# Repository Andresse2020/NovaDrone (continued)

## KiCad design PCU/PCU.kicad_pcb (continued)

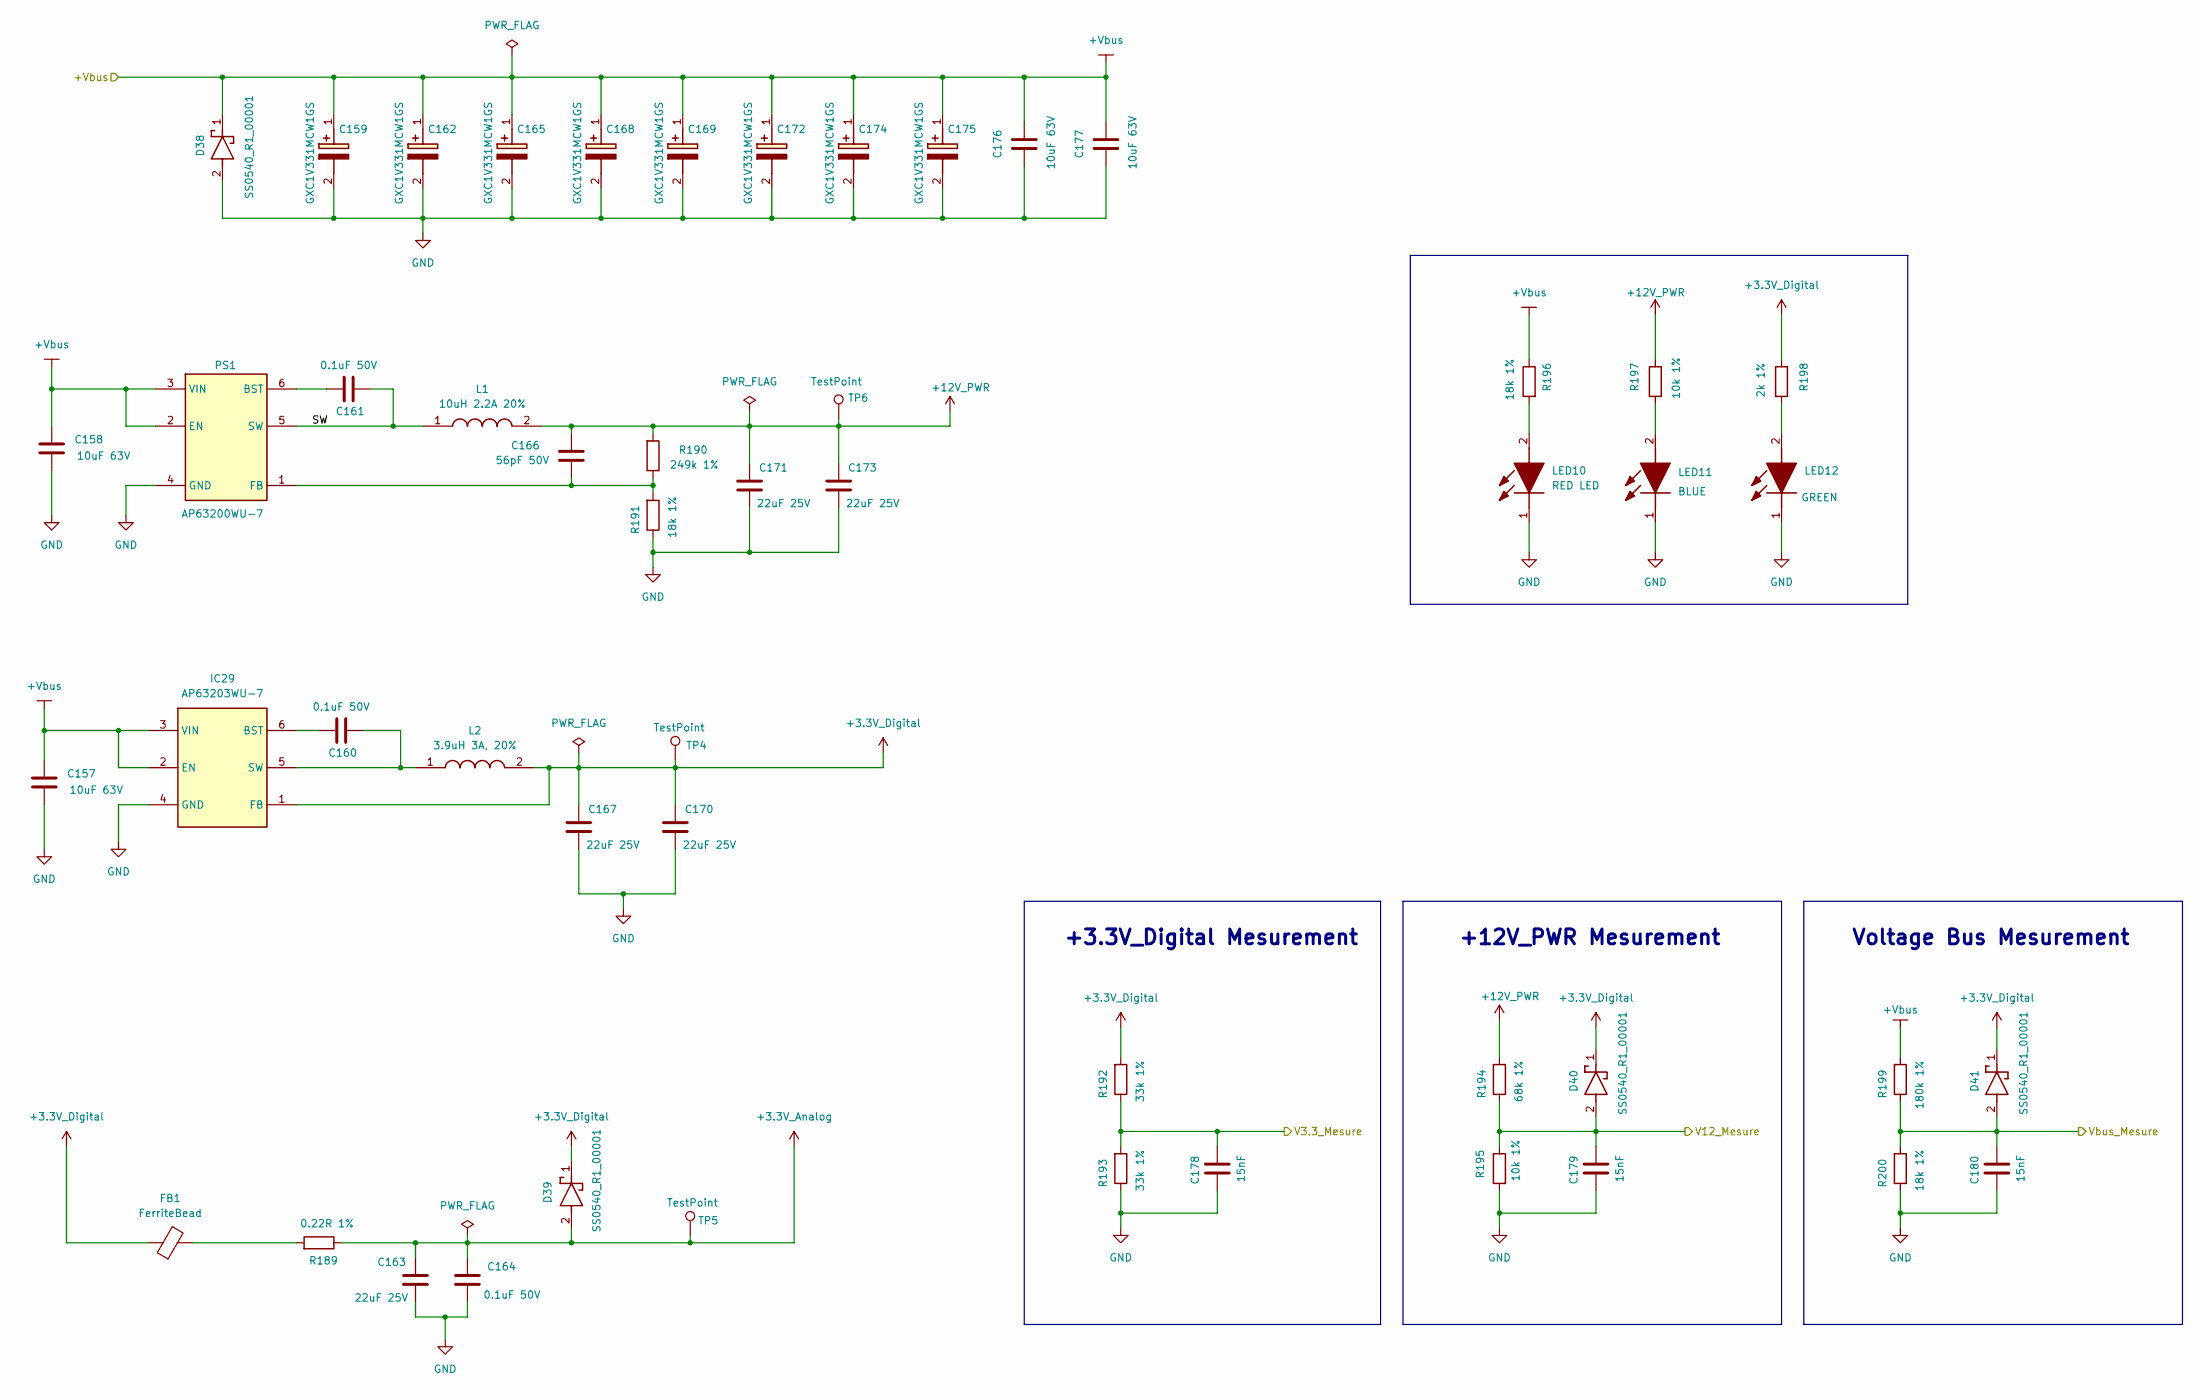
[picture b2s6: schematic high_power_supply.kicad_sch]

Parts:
C157, C158, C176, C177: 10uF 63V; C_1210_3225Metric; Manufacturer_Part_Number CL32B106KMVNNWE
C159, C162, C165, C168, C169, C172, C174, C175: GXC1V331MCW1GS; CAPAE1030X1300N; Mouser Part Number 647-GXC1V331MCW1GS
C160, C161, C164: 0.1uF 50V; C_0603_1608Metric; Manufacturer_Part_Number CL10B104KB85PNL
C163, C167, C170, C171, C173: 22uF 25V; C_1210_3225Metric; Manufacturer_Part_Number CL32B226KAJNNNE
C166: 56pF 50V; C_0603_1608Metric; Manufacturer_Part_Number CL10C560JB8NNNC
C178, C179, C180: 15nF; C_0603_1608Metric; Manufacturer_Part_Number CL10B153KB8NNNC
D38, D39, D40, D41: SS0540_R1_00001; SOD3816X135N; Mouser Part Number 241-SS0540_R1_00001
FB1: FerriteBead; L_0805_2012Metric; Manufacturer_Part_Number MPZ2012S601AT000
IC29: AP63203WU-7; AP63203WU7; Mouser Part Number 621-AP63203WU-7
L1: 10uH 2.2A 20%; BWVS00505040100M00; Manufacturer_Part_Number BWVS00505040100M00
L2: 3.9uH 3A, 20%; ASPI0628150MT1; Mouser Part Number 815-ASPI-0628-3R9MT1
LED10: RED LED; LEDM168X80N; Manufacturer_Part_Number APHD1608LSURCK
LED11: BLUE; LEDM168X80N; Mouser Part Number 604-APHD1608LQBCD
LED12: GREEN; LEDM168X80N; Mouser Part Number 604-APHD1608LZGCK
PS1: AP63200WU-7; SOT95P280X100-6N; Mouser Part Number 621-AP63200WU-7
R189: 0.22R 1%; R_0805_2012Metric; Manufacturer_Part_Number RL0805FR-7W0R22L
R190: 249k 1%; R_0603_1608Metric; Manufacturer_Part_Number AF0603FR-07249KL
R191, R196, R200: 18k 1%; R_0603_1608Metric; Manufacturer_Part_Number AC0603FR-1318KL
R192, R193: 33k 1%; R_0603_1608Metric; Manufacturer_Part_Number AC0603FR-1333KL
R194: 68k 1%; R_0603_1608Metric; Manufacturer_Part_Number RC0603FR-1068KL
R195, R197: 10k 1%; R_0603_1608Metric; Manufacturer_Part_Number AF0603FR-0710KL
R198: 2k 1%; R_0603_1608Metric; Manufacturer_Part_Number RE0603FRE072KL
R199: 180k 1%; R_0603_1608Metric; Manufacturer_Part_Number RT0603FRE07180KL
TP4, TP5, TP6: TestPoint; TestPoint_Pad_D1.0mm

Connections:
+3.3V_Analog: C163.2, C164.2, D39.2 (A), R189.1, TP5.1; also elsewhere on the board
+3.3V_Digital: C167.2, C170.2, D39.1 (K), D40.1 (K), D41.1 (K), FB1.1, IC29.1 (FB), L2.2, R192.2, R198.1, TP4.1; also elsewhere on the board
+12V_PWR: C166.2, C171.2, C173.2, L1.2, R190.2, R194.2, R197.1, TP6.1; also elsewhere on the board
+Vbus: C157.2, C158.2, C159.1 (+), C162.1 (+), C165.1 (+), C168.1 (+), C169.1 (+), C172.1 (+), C174.1 (+), C175.1 (+), C176.2, C177.2, D38.1 (K), IC29.2 (EN), IC29.3 (VIN), PS1.2 (EN), PS1.3 (VIN), R196.1, R199.2; also elsewhere on the board
/HIGH PSU/SW: C161.1, L1.1, PS1.5 (SW)
/HIGH PSU/V3.3_Mesure: C178.2, R192.1, R193.2; also elsewhere on the board
/HIGH PSU/V12_Mesure: C179.2, D40.2 (A), R194.1, R195.1; also elsewhere on the board
/HIGH PSU/Vbus_Mesure: C180.2, D41.2 (A), R199.1, R200.2; also elsewhere on the board
GND: C157.1, C158.1, C159.2 (-), C162.2 (-), C163.1, C164.1, C165.2 (-), C167.1, C168.2 (-), C169.2 (-), C170.1, C171.1, C172.2 (-), C173.1, C174.2 (-), C175.2 (-), C176.1, C177.1, C178.1, C179.1, C180.1, D38.2 (A), IC29.4 (GND), LED10.1 (K), LED11.1 (K), LED12.1 (K), PS1.4 (GND), R191.1, R193.1, R195.2, R200.1; also elsewhere on the board
unnamed: FB1.2, R189.2
unnamed: C160.2, IC29.6 (BST)
unnamed: C160.1, IC29.5 (SW), L2.1
unnamed: LED10.2 (A), R196.2
unnamed: LED11.2 (A), R197.2
unnamed: LED12.2 (A), R198.2
unnamed: C161.2, PS1.6 (BST)
unnamed: C166.1, PS1.1 (FB), R190.1, R191.2

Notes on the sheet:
+3.3V_Digital Mesurement
Voltage Bus Mesurement
+12V_PWR Mesurement

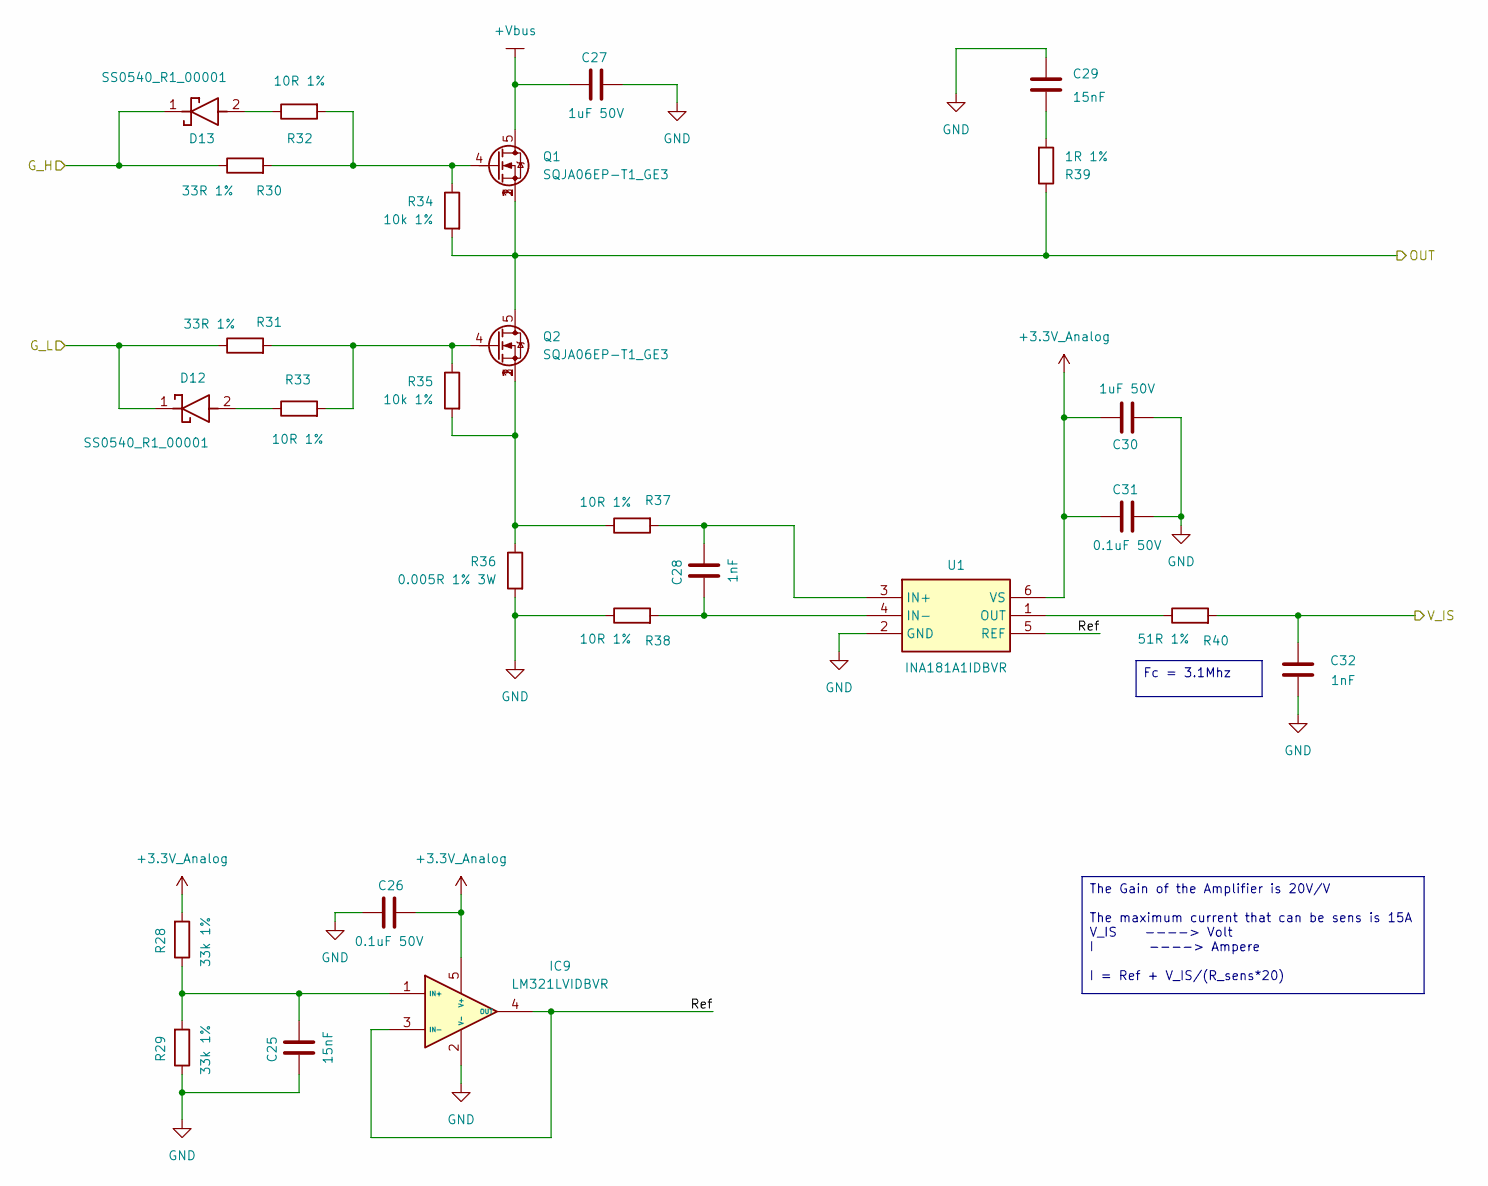
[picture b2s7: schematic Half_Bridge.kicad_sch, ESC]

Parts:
C25, C29: 15nF; C_0603_1608Metric; Manufacturer_Part_Number CL10B153KB8NNNC
C26, C31: 0.1uF 50V; C_0603_1608Metric; Manufacturer_Part_Number CL10B104KB85PNL
C27, C30: 1uF 50V; C_0805_2012Metric; Manufacturer_Part_Number CL21B105KBFNNNE
C28, C32: 1nF; C_0603_1608Metric; Manufacturer_Part_Number KAF15AR71H102KM
D12, D13: SS0540_R1_00001; SOD3816X135N; Mouser Part Number 241-SS0540_R1_00001
IC9: LM321LVIDBVR; SOT95P280X145-5N; Mouser Part Number 595-LM321LVIDBVR
Q1, Q2: SQJA06EP-T1_GE3; SQJ402EPT1; Manufacturer_Part_Number SQJA06EP-T1_GE3
R28, R29: 33k 1%; R_0603_1608Metric; Manufacturer_Part_Number AC0603FR-1333KL
R30, R31: 33R 1%; R_0603_1608Metric; Manufacturer_Part_Number AF0603FR-0733RL
R32, R33, R37, R38: 10R 1%; R_0603_1608Metric; Manufacturer_Part_Number RE0603FRE0710RL
R34, R35: 10k 1%; R_0603_1608Metric; Manufacturer_Part_Number AF0603FR-0710KL
R36: 0.005R 1% 3W; R_2512_6332Metric; Manufacturer_Part_Number MSMA2512R0050FGM
R39: 1R 1%; R_0603_1608Metric; Manufacturer_Part_Number AF0603FR-071RL
R40: 51R 1%; R_0603_1608Metric; Manufacturer_Part_Number RT0603FRE0751RL
U1: INA181A1IDBVR; SOT95P280X145-6N; Mouser Part Number 595-INA181A1IDBVR

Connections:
+3.3V_Analog: C26.1, C30.1, C31.1, IC9.5 (V+), R28.2, U1.6 (VS); also elsewhere on the board
+Vbus: C27.1, Q1.5; also elsewhere on the board
/ESC_2/Current_Sens_2: C32.2, R40.2; also elsewhere on the board
/ESC_2/Half-Bridge_2/G_H: D13.1 (K), R30.1; also elsewhere on the board
/ESC_2/Half-Bridge_2/G_L: D12.1 (K), R31.1; also elsewhere on the board
/ESC_2/Half-Bridge_2/Ref: IC9.3 (IN-), IC9.4 (OUT), U1.5 (REF)
/ESC_2/OUT2: Q1.1, Q1.2, Q1.3, Q2.5, R34.2, R39.1; also elsewhere on the board
GND: C25.1, C26.2, C27.2, C29.1, C30.2, C31.2, C32.1, IC9.2 (V-), R29.1, R36.2, R38.1, U1.2 (GND); also elsewhere on the board
unnamed: C29.2, R39.2
unnamed: D12.2 (A), R33.1
unnamed: D13.2 (A), R32.1
unnamed: C25.2, IC9.1 (IN+), R28.1, R29.2
unnamed: Q1.4, R30.2, R32.2, R34.1
unnamed: Q2.1, Q2.2, Q2.3, R35.2, R36.1, R37.1
unnamed: Q2.4, R31.2, R33.2, R35.1
unnamed: C28.2, R37.2, U1.3 (IN+)
unnamed: C28.1, R38.2, U1.4 (IN-)
unnamed: R40.1, U1.1 (OUT)

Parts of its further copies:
C33, C37, C41, C45, C73, C77, C81, C85, C89, C93, C121, C125, C129, C133, C137, C141, C194, C200, C206, C220, C235, C248: 15nF; C_0603_1608Metric; Manufacturer_Part_Number CL10B153KB8NNNC
C34, C39, C42, C47, C74, C79, C82, C87, C90, C95, C122, C127, C130, C135, C138, C143, C195, C202, C210, C224, C237, C251: 0.1uF 50V; C_0603_1608Metric; Manufacturer_Part_Number CL10B104KB85PNL
C35, C38, C43, C46, C75, C78, C83, C86, C91, C94, C123, C126, C131, C134, C139, C142, C197, C201, C211, C223, C240, C250: 1uF 50V; C_0805_2012Metric; Manufacturer_Part_Number CL21B105KBFNNNE
C36, C40, C44, C48, C76, C80, C84, C88, C92, C96, C124, C128, C132, C136, C140, C144, C198, C204, C216, C228, C242, C253: 1nF; C_0603_1608Metric; Manufacturer_Part_Number KAF15AR71H102KM
D14, D15, D16, D17, D22, D23, D24, D25, D26, D27, D32, D33, D34, D35, D36, D37, D42, D43, D45, D46, D49, D50: SS0540_R1_00001; SOD3816X135N; Mouser Part Number 241-SS0540_R1_00001
IC10, IC11, IC17, IC18, IC19, IC25, IC26, IC27, IC31, IC33, IC37: LM321LVIDBVR; SOT95P280X145-5N; Mouser Part Number 595-LM321LVIDBVR
Q3, Q4, Q5, Q6, Q7, Q8, Q9, Q10, Q11, Q12, Q13, Q14, Q15, Q16, Q17, Q18, Q19, Q20, Q28, Q29, Q30, Q31: SQJA06EP-T1_GE3; SQJ402EPT1; Manufacturer_Part_Number SQJA06EP-T1_GE3
R41, R42, R54, R55, R86, R87, R99, R100, R112, R113, R144, R145, R157, R158, R170, R171, R208, R209, R239, R240, R266, R267: 33k 1%; R_0603_1608Metric; Manufacturer_Part_Number AC0603FR-1333KL
R43, R44, R56, R57, R88, R89, R101, R102, R114, R115, R146, R147, R159, R160, R172, R173, R210, R211, R241, R242, R268, R269: 33R 1%; R_0603_1608Metric; Manufacturer_Part_Number AF0603FR-0733RL
R45, R46, R50, R51, R58, R59, R63, R64, R90, R91, R95, R96, R103, R104, R108, R109, R116, R117, R121, R122, R148, R149, R153, R154, R161, R162, R166, R167, R174, R175, R179, R180, R212, R213, R223, R224, R243, R244, R250, R251, R270, R271, R277, R278: 10R 1%; R_0603_1608Metric; Manufacturer_Part_Number RE0603FRE0710RL
R47, R48, R60, R61, R92, R93, R105, R106, R118, R119, R150, R151, R163, R164, R176, R177, R217, R218, R245, R246, R273, R274: 10k 1%; R_0603_1608Metric; Manufacturer_Part_Number AF0603FR-0710KL
R49, R62, R94, R107, R120, R152, R165, R178, R219, R247, R275: 0.005R 1% 3W; R_2512_6332Metric; Manufacturer_Part_Number MSMA2512R0050FGM
R52, R65, R97, R110, R123, R155, R168, R181, R231, R254, R280: 1R 1%; R_0603_1608Metric; Manufacturer_Part_Number AF0603FR-071RL
R53, R66, R98, R111, R124, R156, R169, R182, R234, R257, R281: 51R 1%; R_0603_1608Metric; Manufacturer_Part_Number RT0603FRE0751RL
U2, U3, U4, U5, U6, U7, U8, U9, U10, U11, U12: INA181A1IDBVR; SOT95P280X145-6N; Mouser Part Number 595-INA181A1IDBVR

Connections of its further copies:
+3.3V_Analog: C34.1, C38.1, C39.1, C42.1, C46.1, C47.1, C74.1, C78.1, C79.1, C82.1, C86.1, C87.1, C90.1, C94.1, C95.1, C122.1, C126.1, C127.1, C130.1, C134.1, C135.1, C138.1, C142.1, C143.1, C195.1, C201.1, C202.1, C210.1, C223.1, C224.1, C237.1, C250.1, C251.1, IC10.5 (V+), IC11.5 (V+), IC17.5 (V+), IC18.5 (V+), IC19.5 (V+), IC25.5 (V+), IC26.5 (V+), IC27.5 (V+), IC31.5 (V+), IC33.5 (V+), IC37.5 (V+), R41.2, R54.2, R86.2, R99.2, R112.2, R144.2, R157.2, R170.2, R208.2, R239.2, R266.2, U2.6 (VS), U3.6 (VS), U4.6 (VS), U5.6 (VS), U6.6 (VS), U7.6 (VS), U8.6 (VS), U9.6 (VS), U10.6 (VS), U11.6 (VS), U12.6 (VS); also elsewhere on the board
+Vbus: C35.1, C43.1, C75.1, C83.1, C91.1, C123.1, C131.1, C139.1, C197.1, C211.1, C240.1, Q3.5, Q5.5, Q7.5, Q9.5, Q11.5, Q13.5, Q15.5, Q17.5, Q19.5, Q28.5, Q30.5; also elsewhere on the board
/ESC_1/Current_Sens_1: C204.2, R234.2; also elsewhere on the board
/ESC_1/Current_Sens_2: C228.2, R257.2; also elsewhere on the board
/ESC_1/Current_Sens_3: C253.2, R281.2; also elsewhere on the board
/ESC_1/Half-Bridge_1/G_H: D43.1 (K), R210.1; also elsewhere on the board
/ESC_1/Half-Bridge_1/G_L: D42.1 (K), R211.1; also elsewhere on the board
/ESC_1/Half-Bridge_1/Ref: IC31.3 (IN-), IC31.4 (OUT), U10.5 (REF)
/ESC_1/Half-Bridge_2/G_H: D46.1 (K), R241.1; also elsewhere on the board
/ESC_1/Half-Bridge_2/G_L: D45.1 (K), R242.1; also elsewhere on the board
/ESC_1/Half-Bridge_2/Ref: IC33.3 (IN-), IC33.4 (OUT), U11.5 (REF)
/ESC_1/Half-Bridge_3/G_H: D50.1 (K), R268.1; also elsewhere on the board
/ESC_1/Half-Bridge_3/G_L: D49.1 (K), R269.1; also elsewhere on the board
/ESC_1/Half-Bridge_3/Ref: IC37.3 (IN-), IC37.4 (OUT), U12.5 (REF)
/ESC_1/OUT1: Q19.1, Q19.2, Q19.3, Q20.5, R217.2, R231.1; also elsewhere on the board
/ESC_1/OUT2: Q28.1, Q28.2, Q28.3, Q29.5, R245.2, R254.1; also elsewhere on the board
/ESC_1/OUT3: Q30.1, Q30.2, Q30.3, Q31.5, R273.2, R280.1; also elsewhere on the board
/ESC_2/Current_Sens_1: C40.2, R53.2; also elsewhere on the board
/ESC_2/Current_Sens_3: C48.2, R66.2; also elsewhere on the board
/ESC_2/Half-Bridge_1/G_H: D15.1 (K), R43.1; also elsewhere on the board
/ESC_2/Half-Bridge_1/G_L: D14.1 (K), R44.1; also elsewhere on the board
/ESC_2/Half-Bridge_1/Ref: IC10.3 (IN-), IC10.4 (OUT), U2.5 (REF)
/ESC_2/Half-Bridge_3/G_H: D17.1 (K), R56.1; also elsewhere on the board
/ESC_2/Half-Bridge_3/G_L: D16.1 (K), R57.1; also elsewhere on the board
/ESC_2/Half-Bridge_3/Ref: IC11.3 (IN-), IC11.4 (OUT), U3.5 (REF)
/ESC_2/OUT1: Q3.1, Q3.2, Q3.3, Q4.5, R47.2, R52.1; also elsewhere on the board
/ESC_2/OUT3: Q5.1, Q5.2, Q5.3, Q6.5, R60.2, R65.1; also elsewhere on the board
/ESC_3/Current_Sens_1: C88.2, R111.2; also elsewhere on the board
/ESC_3/Current_Sens_2: C80.2, R98.2; also elsewhere on the board
/ESC_3/Current_Sens_3: C96.2, R124.2; also elsewhere on the board
/ESC_3/Half-Bridge_1/G_H: D25.1 (K), R101.1; also elsewhere on the board
/ESC_3/Half-Bridge_1/G_L: D24.1 (K), R102.1; also elsewhere on the board
/ESC_3/Half-Bridge_1/Ref: IC18.3 (IN-), IC18.4 (OUT), U5.5 (REF)
/ESC_3/Half-Bridge_2/G_H: D23.1 (K), R88.1; also elsewhere on the board
/ESC_3/Half-Bridge_2/G_L: D22.1 (K), R89.1; also elsewhere on the board
/ESC_3/Half-Bridge_2/Ref: IC17.3 (IN-), IC17.4 (OUT), U4.5 (REF)
/ESC_3/Half-Bridge_3/G_H: D27.1 (K), R114.1; also elsewhere on the board
/ESC_3/Half-Bridge_3/G_L: D26.1 (K), R115.1; also elsewhere on the board
/ESC_3/Half-Bridge_3/Ref: IC19.3 (IN-), IC19.4 (OUT), U6.5 (REF)
/ESC_3/OUT1: Q9.1, Q9.2, Q9.3, Q10.5, R105.2, R110.1; also elsewhere on the board
/ESC_3/OUT2: Q7.1, Q7.2, Q7.3, Q8.5, R92.2, R97.1; also elsewhere on the board
/ESC_3/OUT3: Q11.1, Q11.2, Q11.3, Q12.5, R118.2, R123.1; also elsewhere on the board
/ESC_4/Current_Sens_1: C136.2, R169.2; also elsewhere on the board
/ESC_4/Current_Sens_2: C128.2, R156.2; also elsewhere on the board
/ESC_4/Current_Sens_3: C144.2, R182.2; also elsewhere on the board
/ESC_4/Half-Bridge_1/G_H: D35.1 (K), R159.1; also elsewhere on the board
/ESC_4/Half-Bridge_1/G_L: D34.1 (K), R160.1; also elsewhere on the board
/ESC_4/Half-Bridge_1/Ref: IC26.3 (IN-), IC26.4 (OUT), U8.5 (REF)
/ESC_4/Half-Bridge_2/G_H: D33.1 (K), R146.1; also elsewhere on the board
/ESC_4/Half-Bridge_2/G_L: D32.1 (K), R147.1; also elsewhere on the board
/ESC_4/Half-Bridge_2/Ref: IC25.3 (IN-), IC25.4 (OUT), U7.5 (REF)
/ESC_4/Half-Bridge_3/G_H: D37.1 (K), R172.1; also elsewhere on the board
/ESC_4/Half-Bridge_3/G_L: D36.1 (K), R173.1; also elsewhere on the board
/ESC_4/Half-Bridge_3/Ref: IC27.3 (IN-), IC27.4 (OUT), U9.5 (REF)
/ESC_4/OUT1: Q15.1, Q15.2, Q15.3, Q16.5, R163.2, R168.1; also elsewhere on the board
/ESC_4/OUT2: Q13.1, Q13.2, Q13.3, Q14.5, R150.2, R155.1; also elsewhere on the board
/ESC_4/OUT3: Q17.1, Q17.2, Q17.3, Q18.5, R176.2, R181.1; also elsewhere on the board
GND: C33.1, C34.2, C35.2, C37.1, C38.2, C39.2, C40.1, C41.1, C42.2, C43.2, C45.1, C46.2, C47.2, C48.1, C73.1, C74.2, C75.2, C77.1, C78.2, C79.2, C80.1, C81.1, C82.2, C83.2, C85.1, C86.2, C87.2, C88.1, C89.1, C90.2, C91.2, C93.1, C94.2, C95.2, C96.1, C121.1, C122.2, C123.2, C125.1, C126.2, C127.2, C128.1, C129.1, C130.2, C131.2, C133.1, C134.2, C135.2, C136.1, C137.1, C138.2, C139.2, C141.1, C142.2, C143.2, C144.1, C194.1, C195.2, C197.2, C200.1, C201.2, C202.2, C204.1, C206.1, C210.2, C211.2, C220.1, C223.2, C224.2, C228.1, C235.1, C237.2, C240.2, C248.1, C250.2, C251.2, C253.1, IC10.2 (V-), IC11.2 (V-), IC17.2 (V-), IC18.2 (V-), IC19.2 (V-), IC25.2 (V-), IC26.2 (V-), IC27.2 (V-), IC31.2 (V-), IC33.2 (V-), IC37.2 (V-), R42.1, R49.2, R51.1, R55.1, R62.2, R64.1, R87.1, R94.2, R96.1, R100.1, R107.2, R109.1, R113.1, R120.2, R122.1, R145.1, R152.2, R154.1, R158.1, R165.2, R167.1, R171.1, R178.2, R180.1, R209.1, R219.2, R224.1, R240.1, R247.2, R251.1, R267.1, R275.2, R278.1, U2.2 (GND), U3.2 (GND), U4.2 (GND), U5.2 (GND), U6.2 (GND), U7.2 (GND), U8.2 (GND), U9.2 (GND), U10.2 (GND), U11.2 (GND), U12.2 (GND); also elsewhere on the board
unnamed: C37.2, R52.2
unnamed: C45.2, R65.2
unnamed: C77.2, R97.2
unnamed: C85.2, R110.2
unnamed: C93.2, R123.2
unnamed: C125.2, R155.2
unnamed: C133.2, R168.2
unnamed: C141.2, R181.2
unnamed: C200.2, R231.2
unnamed: C220.2, R254.2
unnamed: C248.2, R280.2
unnamed: D14.2 (A), R46.1
unnamed: D15.2 (A), R45.1
unnamed: D16.2 (A), R59.1
unnamed: D17.2 (A), R58.1
unnamed: D22.2 (A), R91.1
unnamed: D23.2 (A), R90.1
unnamed: D24.2 (A), R104.1
unnamed: D25.2 (A), R103.1
unnamed: D26.2 (A), R117.1
unnamed: D27.2 (A), R116.1
unnamed: D32.2 (A), R149.1
unnamed: D33.2 (A), R148.1
unnamed: D34.2 (A), R162.1
unnamed: D35.2 (A), R161.1
unnamed: D36.2 (A), R175.1
unnamed: D37.2 (A), R174.1
unnamed: D42.2 (A), R213.1
unnamed: D43.2 (A), R212.1
unnamed: D45.2 (A), R244.1
unnamed: D46.2 (A), R243.1
unnamed: D49.2 (A), R271.1
unnamed: D50.2 (A), R270.1
unnamed: C33.2, IC10.1 (IN+), R41.1, R42.2
unnamed: C41.2, IC11.1 (IN+), R54.1, R55.2
unnamed: C73.2, IC17.1 (IN+), R86.1, R87.2
unnamed: C81.2, IC18.1 (IN+), R99.1, R100.2
unnamed: C89.2, IC19.1 (IN+), R112.1, R113.2
unnamed: C121.2, IC25.1 (IN+), R144.1, R145.2
unnamed: C129.2, IC26.1 (IN+), R157.1, R158.2
unnamed: C137.2, IC27.1 (IN+), R170.1, R171.2
unnamed: C194.2, IC31.1 (IN+), R208.1, R209.2
unnamed: C206.2, IC33.1 (IN+), R239.1, R240.2
unnamed: C235.2, IC37.1 (IN+), R266.1, R267.2
unnamed: Q3.4, R43.2, R45.2, R47.1
unnamed: Q4.1, Q4.2, Q4.3, R48.2, R49.1, R50.1
unnamed: Q4.4, R44.2, R46.2, R48.1
unnamed: Q5.4, R56.2, R58.2, R60.1
unnamed: Q6.1, Q6.2, Q6.3, R61.2, R62.1, R63.1
unnamed: Q6.4, R57.2, R59.2, R61.1
unnamed: Q7.4, R88.2, R90.2, R92.1
unnamed: Q8.1, Q8.2, Q8.3, R93.2, R94.1, R95.1
unnamed: Q8.4, R89.2, R91.2, R93.1
unnamed: Q9.4, R101.2, R103.2, R105.1
unnamed: Q10.1, Q10.2, Q10.3, R106.2, R107.1, R108.1
unnamed: Q10.4, R102.2, R104.2, R106.1
unnamed: Q11.4, R114.2, R116.2, R118.1
unnamed: Q12.1, Q12.2, Q12.3, R119.2, R120.1, R121.1
unnamed: Q12.4, R115.2, R117.2, R119.1
unnamed: Q13.4, R146.2, R148.2, R150.1
unnamed: Q14.1, Q14.2, Q14.3, R151.2, R152.1, R153.1
unnamed: Q14.4, R147.2, R149.2, R151.1
unnamed: Q15.4, R159.2, R161.2, R163.1
unnamed: Q16.1, Q16.2, Q16.3, R164.2, R165.1, R166.1
unnamed: Q16.4, R160.2, R162.2, R164.1
unnamed: Q17.4, R172.2, R174.2, R176.1
unnamed: Q18.1, Q18.2, Q18.3, R177.2, R178.1, R179.1
unnamed: Q18.4, R173.2, R175.2, R177.1
unnamed: Q19.4, R210.2, R212.2, R217.1
unnamed: Q20.1, Q20.2, Q20.3, R218.2, R219.1, R223.1
unnamed: Q20.4, R211.2, R213.2, R218.1
unnamed: Q28.4, R241.2, R243.2, R245.1
unnamed: Q29.1, Q29.2, Q29.3, R246.2, R247.1, R250.1
unnamed: Q29.4, R242.2, R244.2, R246.1
unnamed: Q30.4, R268.2, R270.2, R273.1
unnamed: Q31.1, Q31.2, Q31.3, R274.2, R275.1, R277.1
unnamed: Q31.4, R269.2, R271.2, R274.1
unnamed: C36.2, R50.2, U2.3 (IN+)
unnamed: C36.1, R51.2, U2.4 (IN-)
unnamed: R53.1, U2.1 (OUT)
unnamed: C44.2, R63.2, U3.3 (IN+)
unnamed: C44.1, R64.2, U3.4 (IN-)
unnamed: R66.1, U3.1 (OUT)
unnamed: C76.2, R95.2, U4.3 (IN+)
unnamed: C76.1, R96.2, U4.4 (IN-)
unnamed: R98.1, U4.1 (OUT)
unnamed: C84.2, R108.2, U5.3 (IN+)
unnamed: C84.1, R109.2, U5.4 (IN-)
unnamed: R111.1, U5.1 (OUT)
unnamed: C92.2, R121.2, U6.3 (IN+)
unnamed: C92.1, R122.2, U6.4 (IN-)
unnamed: R124.1, U6.1 (OUT)
unnamed: C124.2, R153.2, U7.3 (IN+)
unnamed: C124.1, R154.2, U7.4 (IN-)
unnamed: R156.1, U7.1 (OUT)
unnamed: C132.2, R166.2, U8.3 (IN+)
unnamed: C132.1, R167.2, U8.4 (IN-)
unnamed: R169.1, U8.1 (OUT)
unnamed: C140.2, R179.2, U9.3 (IN+)
unnamed: C140.1, R180.2, U9.4 (IN-)
unnamed: R182.1, U9.1 (OUT)
unnamed: C198.2, R223.2, U10.3 (IN+)
unnamed: C198.1, R224.2, U10.4 (IN-)
unnamed: R234.1, U10.1 (OUT)
unnamed: C216.2, R250.2, U11.3 (IN+)
unnamed: C216.1, R251.2, U11.4 (IN-)
unnamed: R257.1, U11.1 (OUT)
unnamed: C242.2, R277.2, U12.3 (IN+)
unnamed: C242.1, R278.2, U12.4 (IN-)
unnamed: R281.1, U12.1 (OUT)

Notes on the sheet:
Fc = 3.1Mhz
The Gain of the Amplifier is 20V/V The maximum current that can be sens is 15A V_IS ----> Volt I ----> Ampere I = Ref + V_IS/(R_sens*20)
